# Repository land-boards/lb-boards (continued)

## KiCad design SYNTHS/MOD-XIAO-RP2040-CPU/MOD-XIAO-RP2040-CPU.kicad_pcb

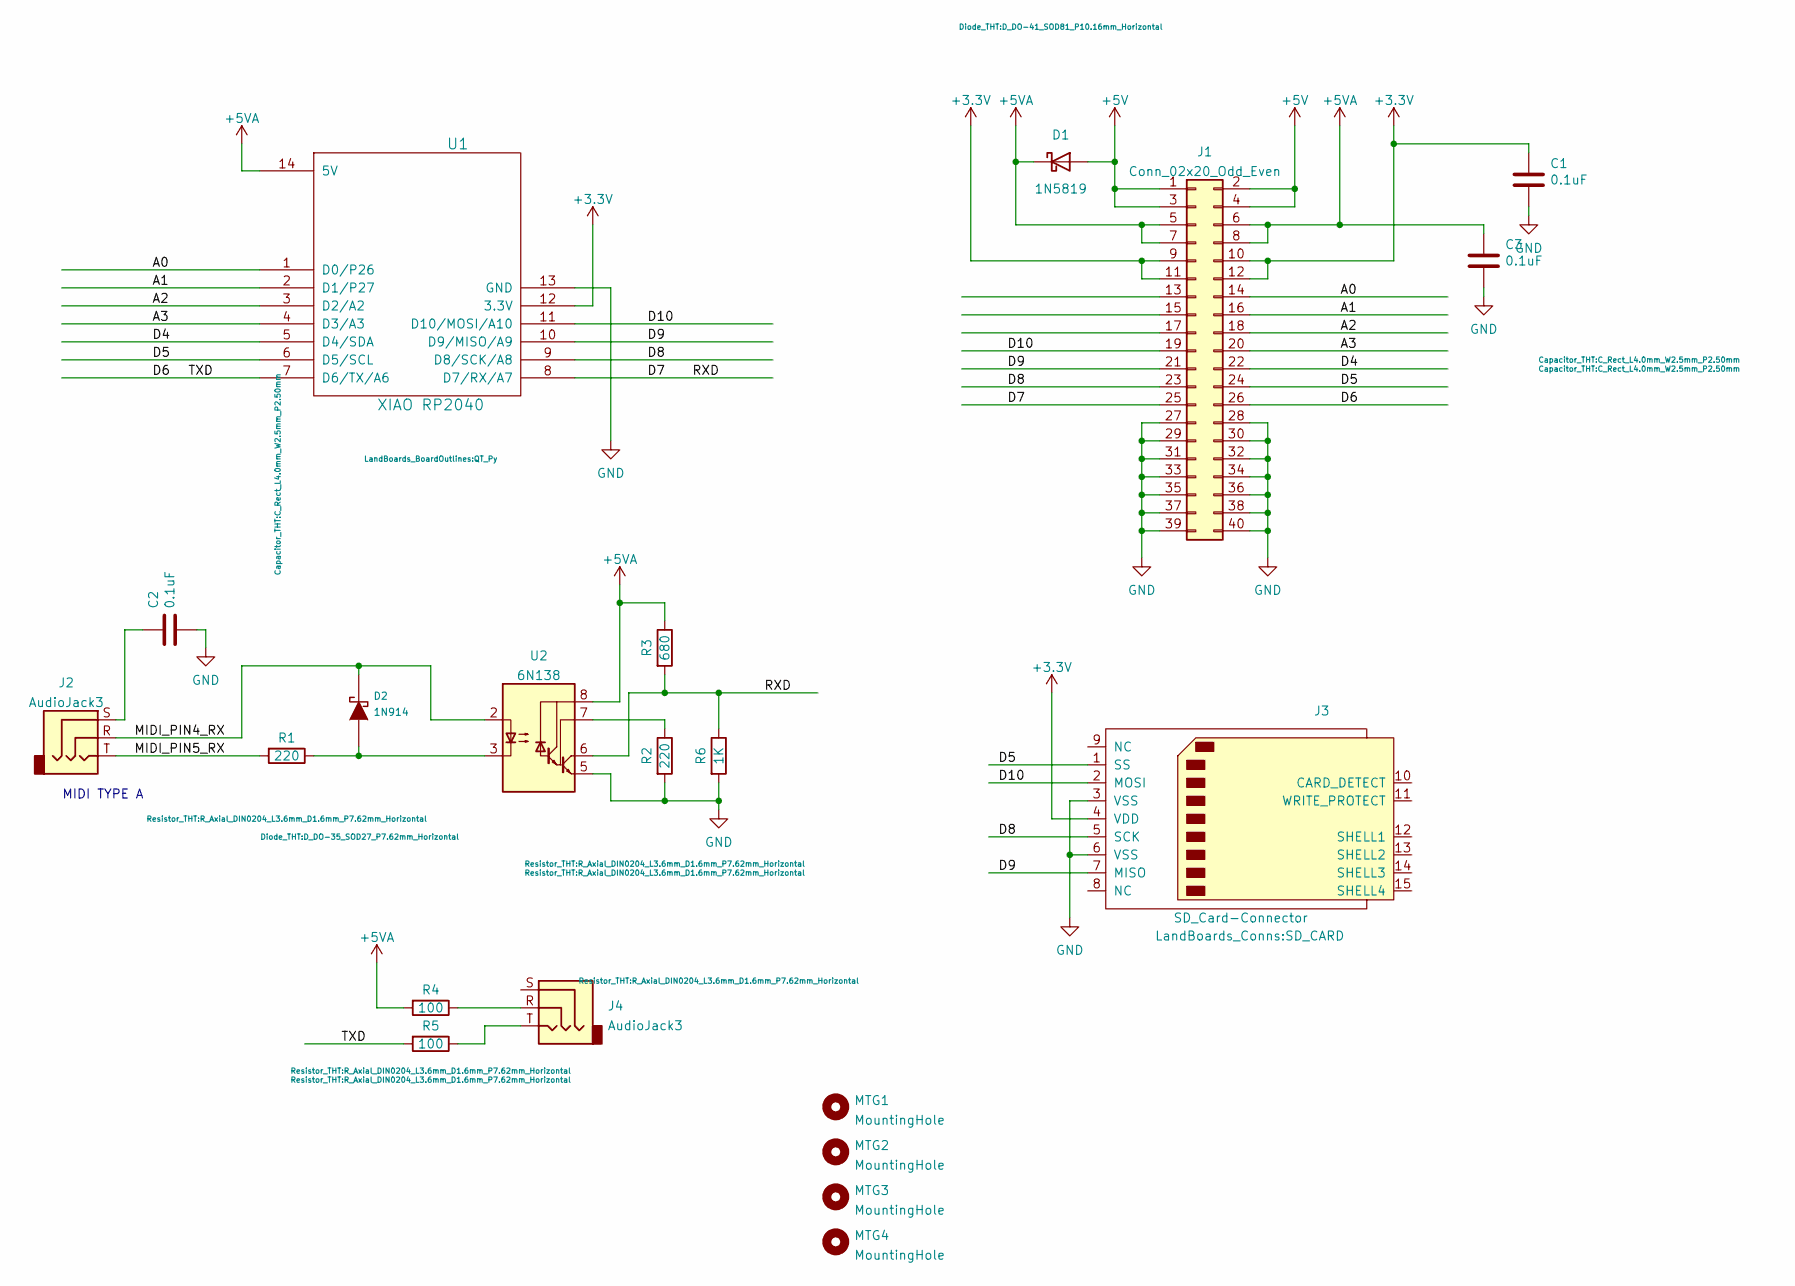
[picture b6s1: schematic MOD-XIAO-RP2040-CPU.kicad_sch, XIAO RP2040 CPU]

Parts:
C1, C2, C3: 0.1uF; C_Rect_L4.0mm_W2.5mm_P2.50mm
D1: 1N5819; D_DO-41_SOD81_P10.16mm_Horizontal
D2: 1N914; D_DO-35_SOD27_P7.62mm_Horizontal
J1: Conn_02x20_Odd_Even; PinHeader_2x20_P2.54mm_Vertical
J2, J4: AudioJack3; Jack_3.5mm_CUI_SJ1-3523N_Horizontal
J3: SD_Card-Connector; SD_CARD
MTG1, MTG2, MTG3, MTG4: MountingHole; MTG-4-40
R1, R2: 220; R_Axial_DIN0204_L3.6mm_D1.6mm_P7.62mm_Horizontal
R3: 680; R_Axial_DIN0204_L3.6mm_D1.6mm_P7.62mm_Horizontal
R4, R5: 100; R_Axial_DIN0204_L3.6mm_D1.6mm_P7.62mm_Horizontal
R6: 1K; R_Axial_DIN0204_L3.6mm_D1.6mm_P7.62mm_Horizontal
U1: XIAO RP2040; QT_Py
U2: 6N138; DIP-8_W7.62mm_Socket_LongPads

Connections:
+3V3: C1.1, J1.9, J1.10, J1.11, J1.12, J3.4 (VDD), U1.12 (3.3V)
+5V: D1.2 (A), J1.1, J1.2, J1.3, J1.4
+5VA: C3.1, D1.1 (K), J1.5, J1.6, J1.7, J1.8, R3.1, R4.2, U1.14 (5V), U2.8 (VCC)
/A0: J1.14, U1.1 (D0/P26)
/A1: J1.16, U1.2 (D1/P27)
/A2: J1.18, U1.3 (D2/A2)
/A3: J1.20, U1.4 (D3/A3)
/D4: J1.22, U1.5 (D4/SDA)
/D5: J1.24, J3.1 (SS), U1.6 (D5/SCL)
/D6: J1.26, R5.2, U1.7 (D6/TX/A6)
/D7: J1.25, R3.2, R6.1, U1.8 (D7/RX/A7), U2.6 (VO2)
/D8: J1.23, J3.5 (SCK), U1.9 (D8/SCK/A8)
/D9: J1.21, J3.7 (MISO), U1.10 (D9/MISO/A9)
/D10: J1.19, J3.2 (MOSI), U1.11 (D10/MOSI/A10)
/MIDI_PIN4_RX: D2.1 (K), J2.R, U2.2 (C1)
/MIDI_PIN5_RX: J2.T, R1.2
GND: C1.2, C2.2, C3.2, J1.27, J1.28, J1.29, J1.30, J1.31, J1.32, J1.33, J1.34, J1.35, J1.36, J1.37, J1.38, J1.39, J1.40, J3.3 (VSS), J3.6 (VSS), R2.2, R6.2, U1.13 (GND), U2.5 (GND)
unnamed: D2.2 (A), R1.1, U2.3 (C2)
unnamed: C2.1, J2.S
unnamed: J4.R, R4.1
unnamed: J4.T, R5.1
unnamed: R2.1, U2.7 (VO1)

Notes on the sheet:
MIDI TYPE A

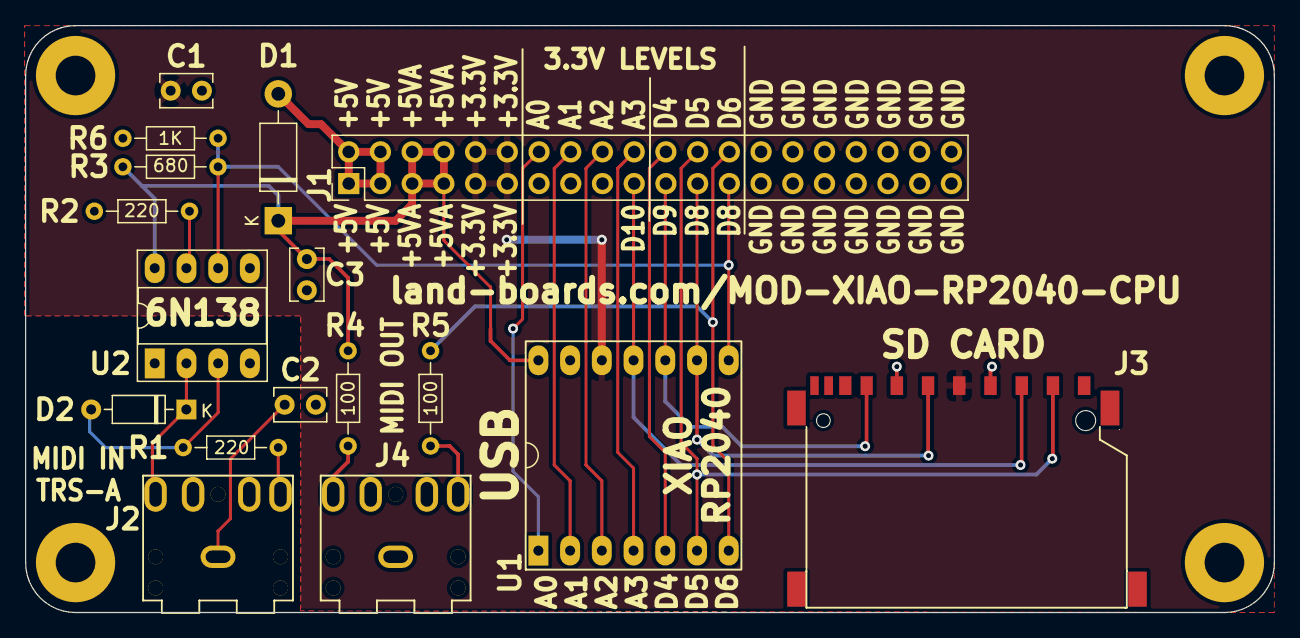
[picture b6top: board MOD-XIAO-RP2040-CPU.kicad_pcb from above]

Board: 2 copper layers, 100.0 x 47.0 mm, 21 parts (0 on the bottom side), 22 nets.

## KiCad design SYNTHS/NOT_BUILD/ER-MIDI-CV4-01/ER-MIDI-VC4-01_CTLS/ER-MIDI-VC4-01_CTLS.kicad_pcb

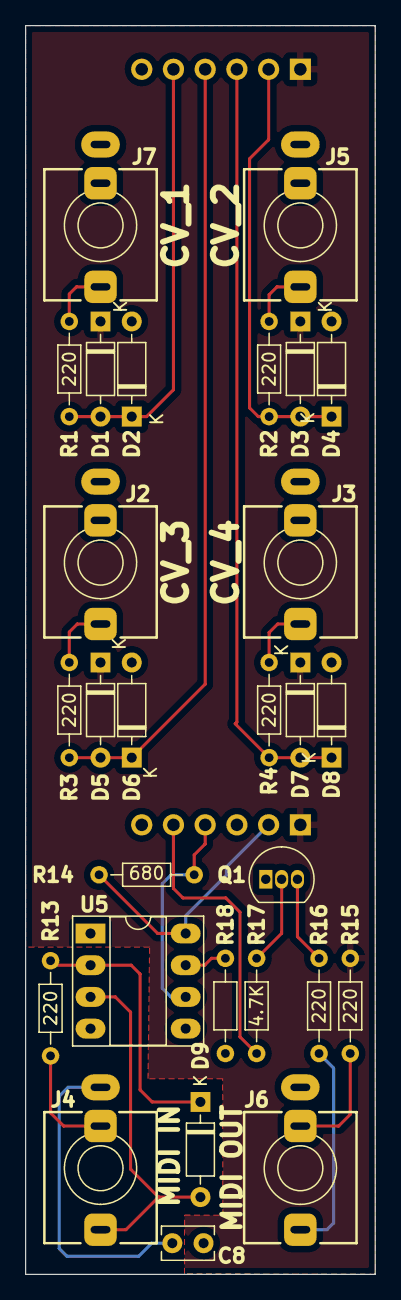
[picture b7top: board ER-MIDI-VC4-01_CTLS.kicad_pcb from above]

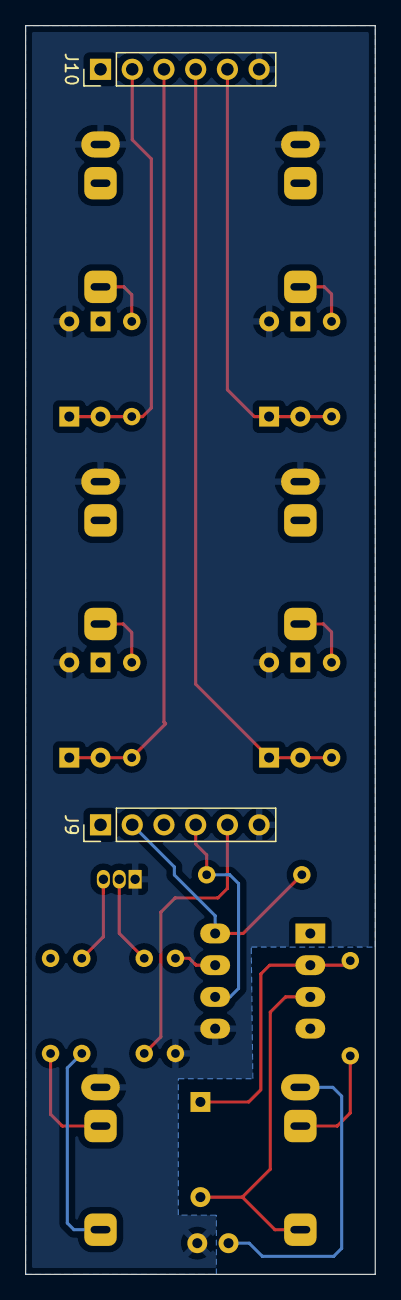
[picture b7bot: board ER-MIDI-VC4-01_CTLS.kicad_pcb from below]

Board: 2 copper layers, 28.0 x 100.0 mm, 30 parts (2 on the bottom side), 22 nets.

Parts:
C8: 0.1uF; C_Rect_L4.0mm_W2.5mm_P2.50mm
D1, D2, D3, D4, D5, D6, D7, D8, D9: BAT41; D_DO-35_SOD27_P7.62mm_Horizontal
J2, J3, J4, J5, J6, J7: AudioJack3; Jack_3.5mm_QingPu_WQP-PJ366ST_Vertical
J9, J10: Conn_01x06; PinHeader_1x06_P2.54mm_Vertical
Q1: 2N3904; TO-92_Inline
R1, R2, R3, R4, R13, R15, R16: 220; R_Axial_DIN0204_L3.6mm_D1.6mm_P7.62mm_Horizontal
R14: 680; R_Axial_DIN0204_L3.6mm_D1.6mm_P7.62mm_Horizontal
R17: 4.7K; R_Axial_DIN0204_L3.6mm_D1.6mm_P7.62mm_Horizontal
R18: 1K; R_Axial_DIN0204_L3.6mm_D1.6mm_P7.62mm_Horizontal
U5: 6N138; DIP-8_W7.62mm_Socket_LongPads

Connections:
+3V3: J9.2, R14.2, U5.8 (VCC)
+5V: D1.1 (K), D3.1 (K), D5.1 (K), D7.1 (K), J9.1, J10.1, R15.2
/CV1: J7.T, R1.2
/CV1_C: D1.2 (A), D2.1 (K), J10.5, R1.1
/CV2: J5.T, R2.2
/CV2_C: D3.2 (A), D4.1 (K), J10.2, R2.1
/CV3: J2.T, R3.2
/CV3_C: D5.2 (A), D6.1 (K), J10.4, R3.1
/CV4: J3.T, R4.2
/CV4_C: D7.2 (A), D8.1 (K), J10.3, R4.1
/MIDI_GND: C8.1, J4.S
/MIDI_IN: J4.R, R13.1
/MIDI_RES: D9.1 (K), R13.2, U5.2 (C1)
/MIDI_RTN: D9.2 (A), J4.T, U5.3 (C2)
/MO5: J6.R, R15.1
/MOLO: J6.T, R16.2
/OBF: R18.1, U5.7 (VO1)
/OPTOUT-C: J9.4, R14.1, U5.6 (VO2)
/RBI-C: J9.5, R17.2
/RBO: Q1.2 (B), R17.1
GND: C8.2, D2.2 (A), D4.2 (A), D6.2 (A), D8.2 (A), J2.S, J3.S, J5.S, J6.S, J7.S, J9.6, J10.6, Q1.1 (E), R18.2, U5.5 (GND)
unnamed: Q1.3 (C), R16.1

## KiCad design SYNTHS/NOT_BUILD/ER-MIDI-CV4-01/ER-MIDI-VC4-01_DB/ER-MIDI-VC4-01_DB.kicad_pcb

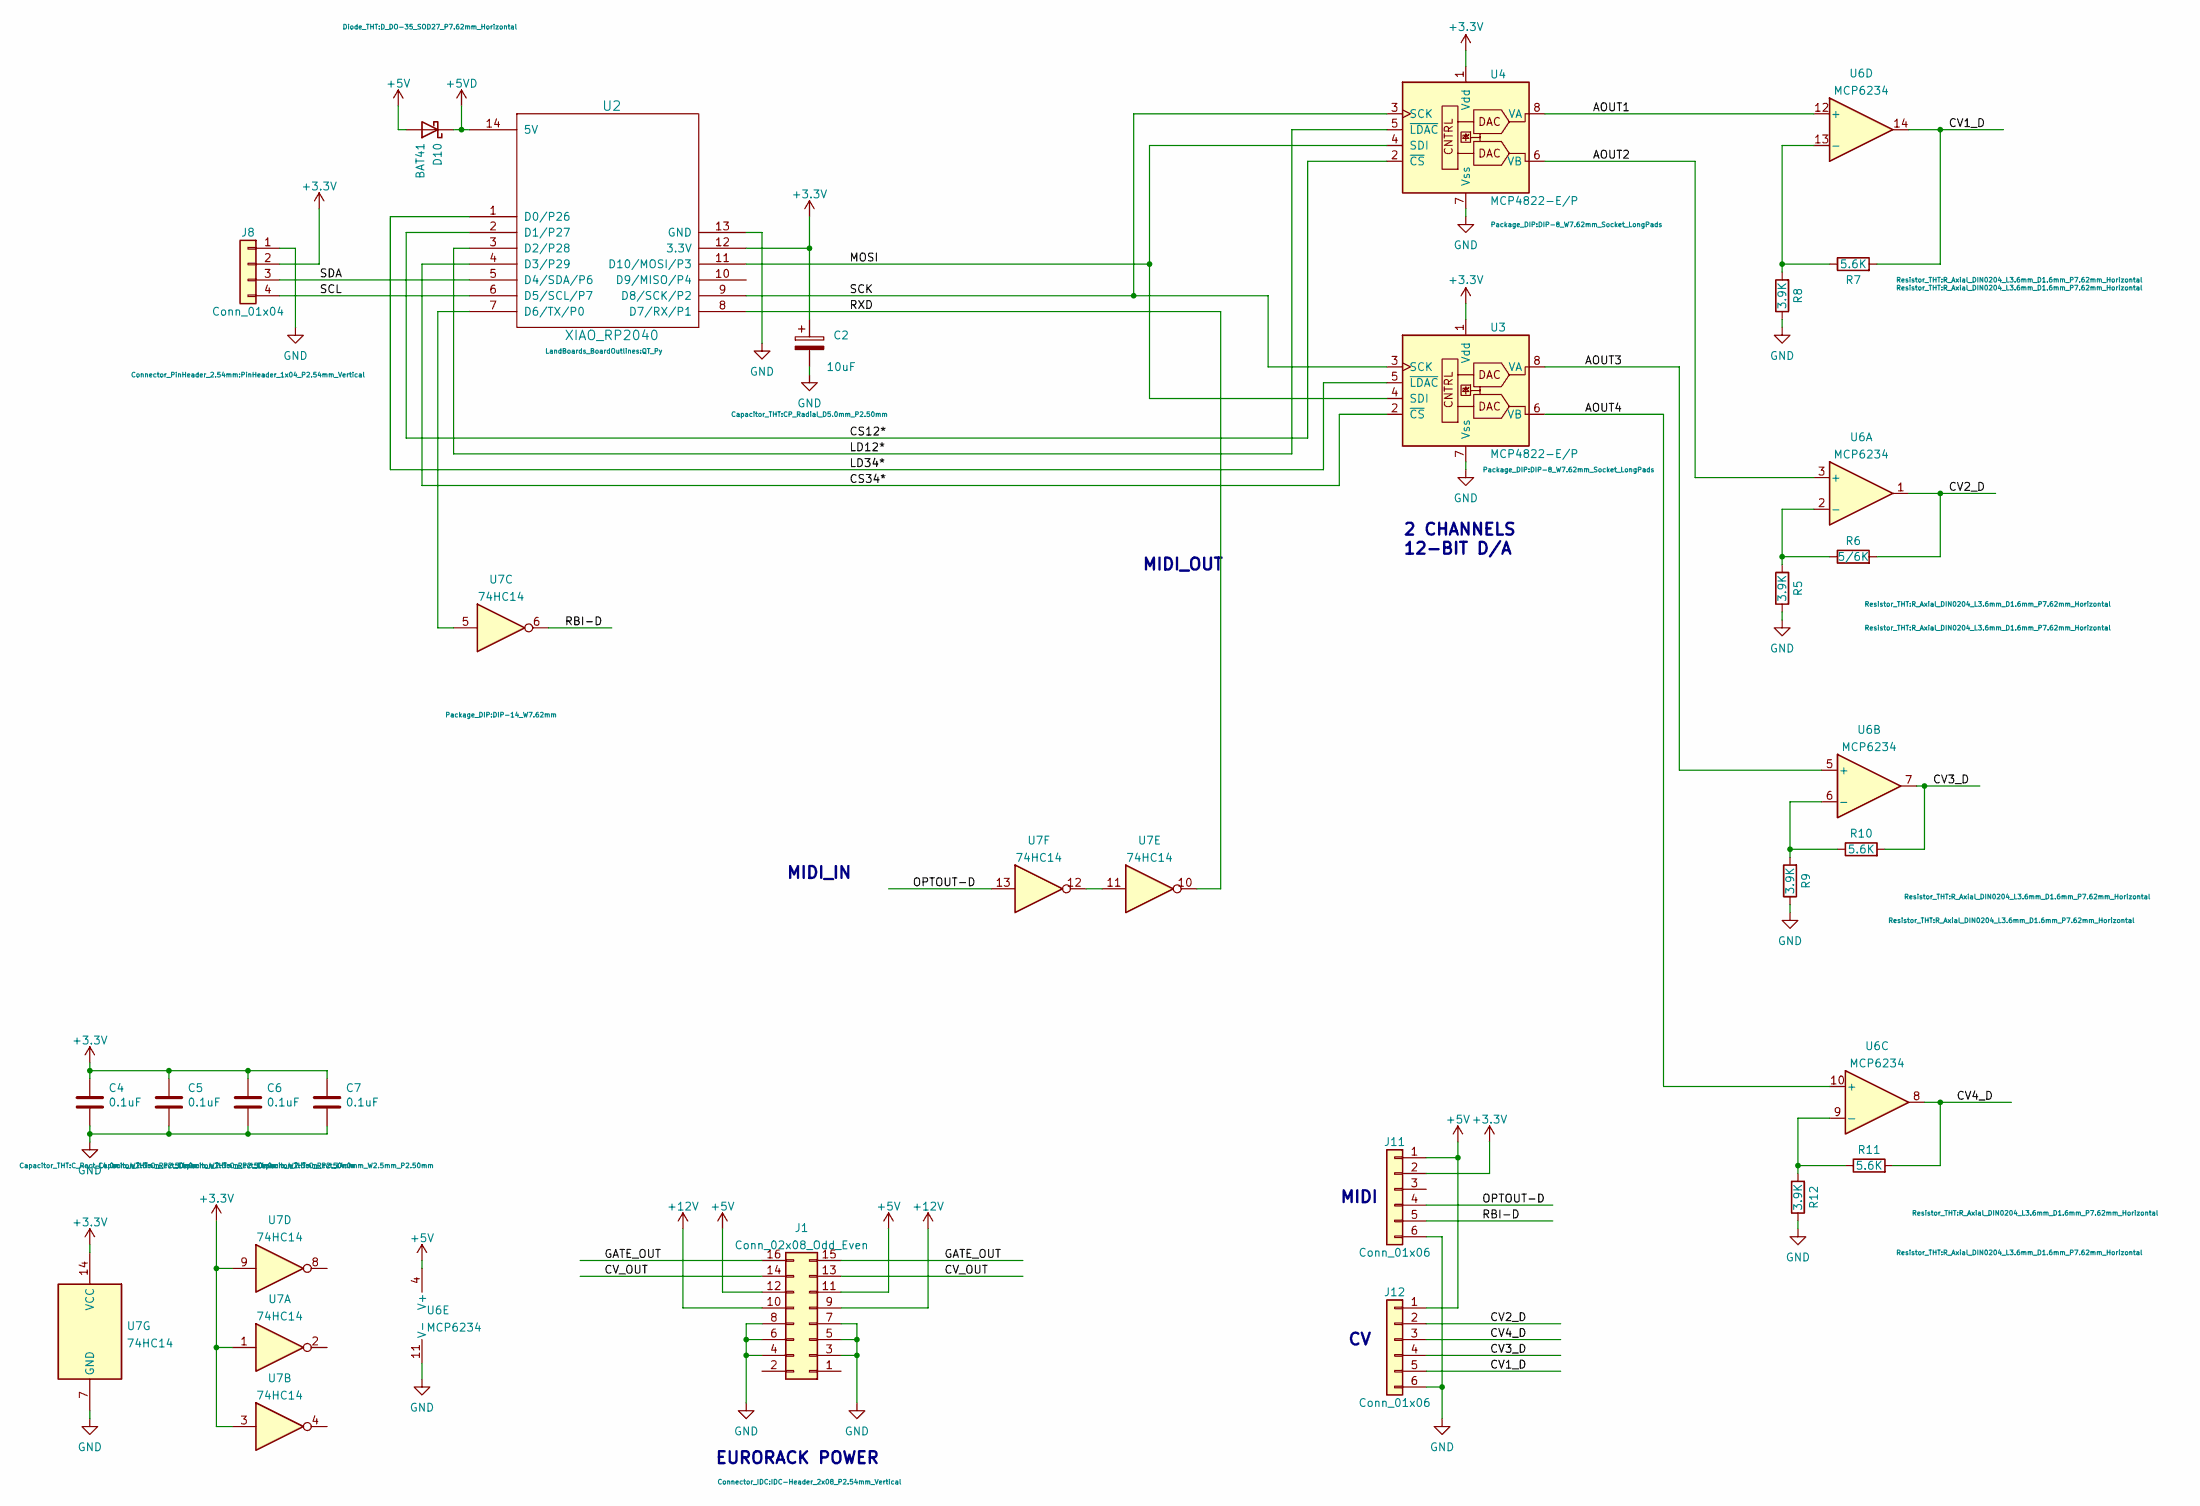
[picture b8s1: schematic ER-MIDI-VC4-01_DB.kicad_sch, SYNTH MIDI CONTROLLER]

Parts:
C2: 10uF; CP_Radial_D5.0mm_P2.50mm
C4, C5, C6, C7: 0.1uF; C_Rect_L4.0mm_W2.5mm_P2.50mm
D10: BAT41; D_DO-35_SOD27_P7.62mm_Horizontal
J1: Conn_02x08_Odd_Even; IDC-Header_2x08_P2.54mm_Vertical
J8: Conn_01x04; PinHeader_1x04_P2.54mm_Vertical
J11, J12: Conn_01x06; PinHeader_1x06_P2.54mm_Vertical
R5, R8, R9, R12: 3.9K; R_Axial_DIN0204_L3.6mm_D1.6mm_P7.62mm_Horizontal
R6: 5/6K; R_Axial_DIN0204_L3.6mm_D1.6mm_P7.62mm_Horizontal
R7, R10, R11: 5.6K; R_Axial_DIN0204_L3.6mm_D1.6mm_P7.62mm_Horizontal
U2: XIAO_RP2040; QT_Py
U3, U4: MCP4822-E/P; DIP-8_W7.62mm_Socket_LongPads
U6: MCP6234; DIP-14_W7.62mm
U7: 74HC14; DIP-14_W7.62mm

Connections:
+3V3: C2.1, C4.1, C5.1, C6.1, C7.1, J8.2, J11.2, U2.12 (3.3V), U3.1 (Vdd), U4.1 (Vdd), U7.1, U7.3, U7.9, U7.14 (VCC)
+5V: D10.2 (A), J1.11, J1.12, J11.1, J12.1, U6.4 (V+)
+5VD: D10.1 (K), U2.14 (5V)
+12V: J1.9, J1.10
/AOUT1: U4.8 (VA), U6.12 (+)
/AOUT2: U4.6 (VB), U6.3 (+)
/AOUT3: U3.8 (VA), U6.5 (+)
/AOUT4: U3.6 (VB), U6.10 (+)
/CS12*: U2.2 (D1/P27), U4.2 (~CS)
/CS34*: U2.4 (D3/P29), U3.2 (~CS)
/CV1_D: J12.5, R7.2, U6.14
/CV2_D: J12.2, R6.2, U6.1
/CV3_D: J12.4, R10.2, U6.7
/CV4_D: J12.3, R11.2, U6.8
/CV_OUT: J1.13, J1.14
/GATE_OUT: J1.15, J1.16
/LD12*: U2.3 (D2/P28), U4.5 (~LDAC)
/LD34*: U2.1 (D0/P26), U3.5 (~LDAC)
/MOSI: U2.11 (D10/MOSI/P3), U3.4 (SDI), U4.4 (SDI)
/OPTOUT-D: J11.4, U7.13
/RBI-D: J11.5, U7.6
/RXD: U2.8 (D7/RX/P1), U7.10
/SCK: U2.9 (D8/SCK/P2), U3.3 (SCK), U4.3 (SCK)
/SCL: J8.4, U2.6 (D5/SCL/P7)
/SDA: J8.3, U2.5 (D4/SDA/P6)
GND: C2.2, C4.2, C5.2, C6.2, C7.2, J1.3, J1.4, J1.5, J1.6, J1.7, J1.8, J8.1, J11.6, J12.6, R5.1, R8.1, R9.1, R12.1, U2.13 (GND), U3.7 (Vss), U4.7 (Vss), U6.11 (V-), U7.7 (GND)
unnamed: R5.2, R6.1, U6.2 (-)
unnamed: R7.1, R8.2, U6.13 (-)
unnamed: R9.2, R10.1, U6.6 (-)
unnamed: R11.1, R12.2, U6.9 (-)
unnamed: U2.7 (D6/TX/P0), U7.5
unnamed: U7.11, U7.12

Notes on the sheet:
MIDI_IN
2 CHANNELS 12-BIT D/A
MIDI_OUT
MIDI
EURORACK POWER

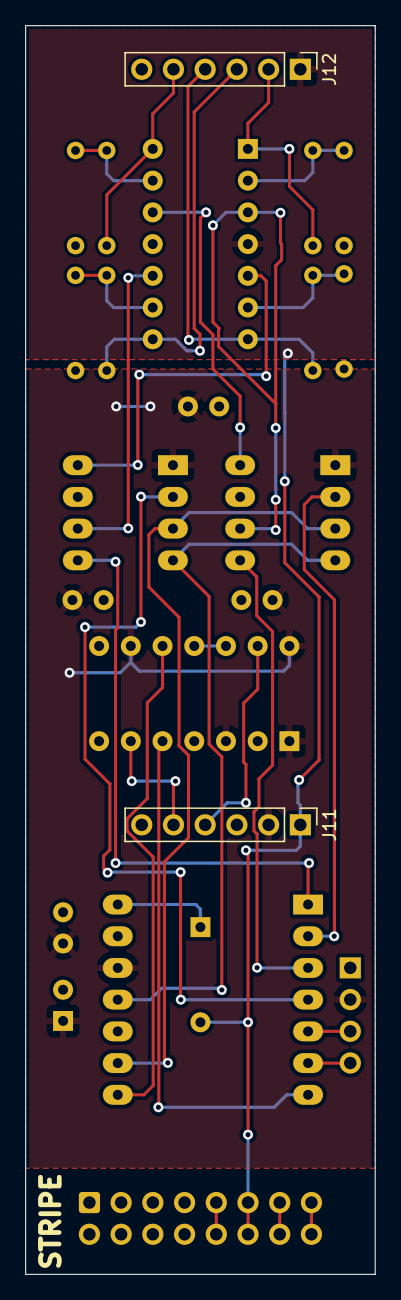
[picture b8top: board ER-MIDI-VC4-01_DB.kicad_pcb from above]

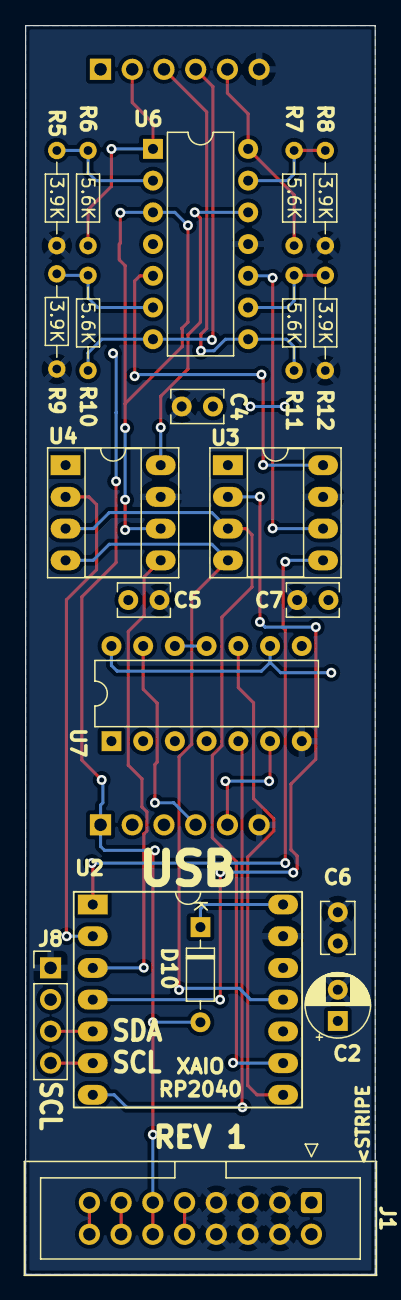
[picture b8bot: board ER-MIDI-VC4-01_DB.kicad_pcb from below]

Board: 2 copper layers, 28.0 x 100.0 mm, 23 parts (21 on the bottom side), 32 nets.
